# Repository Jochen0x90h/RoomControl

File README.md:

RoomControl
===========
Smart home room controller based on nRF52840 with MQTT and and IEEE 802.15.4 radio support. 
Buttons and relays for lights and blinds can also be connected with a local bus using 
LIN physical layer.

Control
-------
This is a 3D printed box with a display and digital potentiometer that gets installed in each
room instead of the floor heating thermostat. It can control the heating valve using an opto-triac,
connect to light and blind switches and relays using LIN physical layer and to battery-free switches
(EnOcan) using an IEEE 802.15.4 radio interface.

Switch
------
This is a wall switch and actor for lights and blinds that can be mounted behind Eltako E-Design
frames and rockers. It connects to the Control via a bus based on LIN physical layer.

Gateway
-------
This is a hat for rpi or compatible single board computers that connects to multiple Controls
via a IEEE 802.15.4 radio network and to an MQTT broker such as mosquitto.

License
-------
This work is licensed under a
[Creative Commons Attribution-NonCommercial-ShareAlike 4.0 International License][cc-by-nc-sa].

[![CC BY-NC-SA 4.0][cc-by-nc-sa-image]][cc-by-nc-sa]

[cc-by-nc-sa]: http://creativecommons.org/licenses/by-nc-sa/4.0/
[cc-by-nc-sa-image]: https://licensebuttons.net/l/by-nc-sa/4.0/88x31.png

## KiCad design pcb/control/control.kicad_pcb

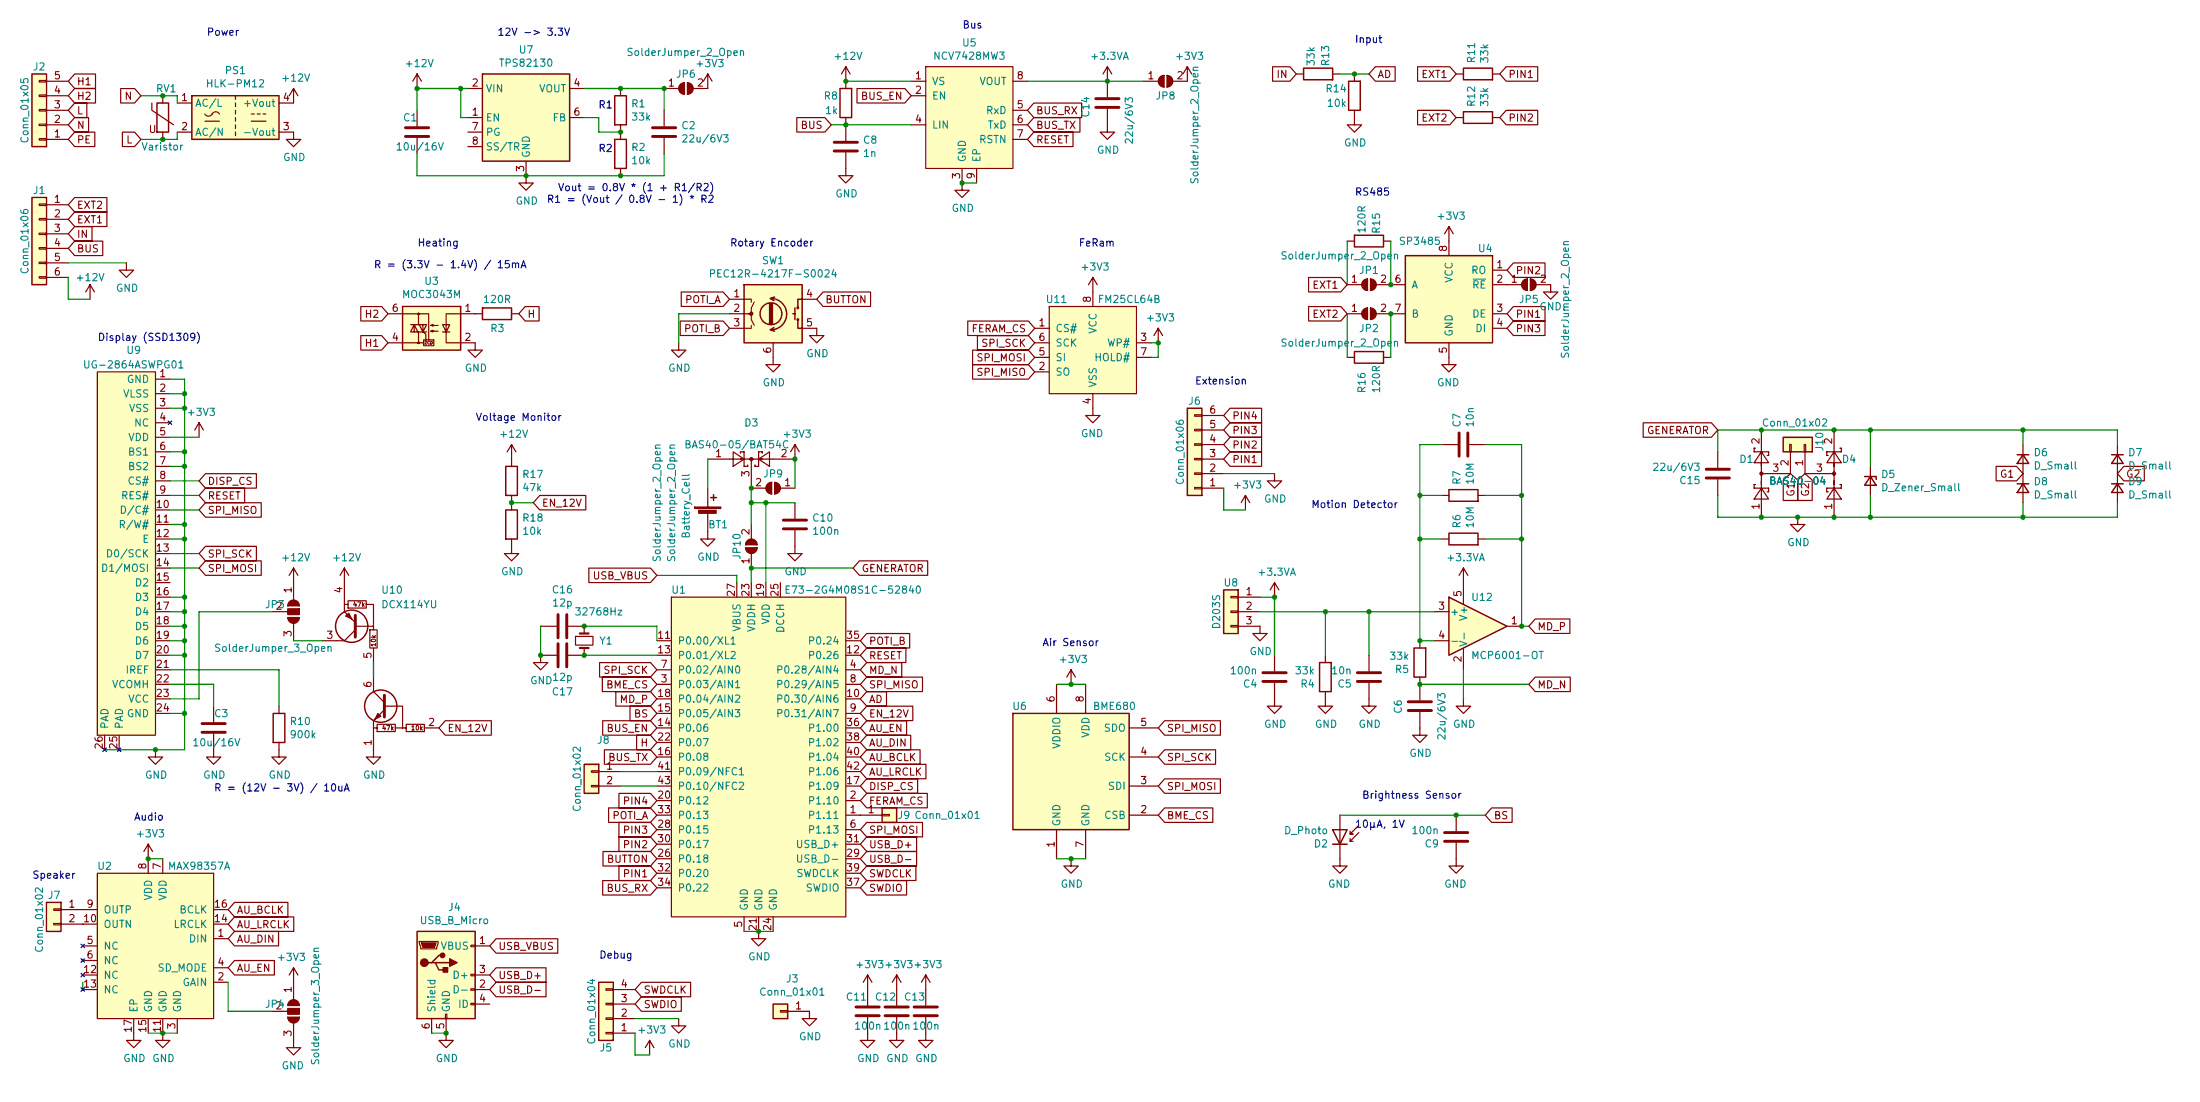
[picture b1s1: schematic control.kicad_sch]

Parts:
BT1: Battery_Cell; Battery_2032
C1, C3: 10u/16V; C_1206_3216Metric
C2, C6, C14, C15: 22u/6V3; C_0805_2012Metric
C4, C9, C10, C11, C12, C13: 100n; C_0603_1608Metric
C5, C7: 10n; C_0603_1608Metric
C8: 1n; C_0603_1608Metric
C16, C17: 12p; C_0603_1608Metric
D1, D4: BAS40-04; SOT-23
D2: D_Photo; DiodeHoles
D3: BAS40-05/BAT54C; SOT-23
D5: D_Zener_Small; D_SOD-323F
D6, D7, D8, D9: D_Small; D_1206_3216Metric_Castellated
J1: Conn_01x06; Wago_236-406
J2: Conn_01x05; Wago_236-405
J3: Conn_01x01; PinHeader_1x01_P2.54mm_Vertical
J4: USB_B_Micro; USB_Micro-B
J5: Conn_01x04; PinHeader_1x04_P2.00mm_Vertical
J6: Conn_01x06; PinHeader_1x06_P2.54mm_Vertical
J7, J10: Conn_01x02; PinHeader_1x02_P2.54mm_Vertical
J8: Conn_01x02; PinHeader_1x02_P2.00mm_Vertical
J9: Conn_01x01; TestPoint_Pad_1.5x1.5mm
JP1, JP2, JP5, JP6, JP8, JP9, JP10: SolderJumper_2_Open; Jumper2
JP3, JP4: SolderJumper_3_Open; Jumper3
PS1: HLK-PM12; HLK-PMxx
R1, R4, R5: 33k; R_0603_1608Metric
R2, R14, R18: 10k; R_0603_1608Metric
R3, R15, R16: 120R; R_1206_3216Metric
R6, R7: 10M; R_0603_1608Metric
R8: 1k; R_1206_3216Metric
R10: 900k; R_0603_1608Metric
R11, R12, R13: 33k; R_1206_3216Metric
R17: 47k; R_0603_1608Metric
RV1: Varistor; S10K275
SW1: PEC12R-4217F-S0024; PEC12R
U1: E73-2G4M08S1C-52840
U2: MAX98357A
U3: MOC3043M
U4: SP3485; SOIC-8_3.9x4.9mm_P1.27mm
U5: NCV7428MW3; NCV7428MW
U6: BME680
U7: TPS82130
U8: D203S
U9: UG-2864ASWPG01; Connector-Flat-24_P0.5mm
U10: DCX114YU; SOT-363_SC-70-6
U11: FM25CL64B
U12: MCP6001-OT; SOT-23-5
Y1: 32768Hz; Crystal_DS26_D2.0mm_L6.0mm_Vertical

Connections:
+3.3VA: C4.2, C14.2, JP8.1 (A), U5.8 (VOUT), U8.1, U12.5 (V+)
+3V3: C11.2, C12.2, C13.2, D3.2, J5.1, J6.1, JP4.1 (A), JP6.2 (B), JP8.2 (B), JP9.1 (A), U2.7 (VDD), U2.8 (VDD), U4.8 (VCC), U6.6 (VDDIO), U6.8 (VDD), U9.5 (VDD), U11.3 (WP#), U11.7 (HOLD#), U11.8 (VCC)
+12V: C1.1, J1.6, JP3.1 (A), PS1.4 (+Vout), R8.2, R17.1, U5.1 (VS), U7.1 (EN), U7.2 (VIN), U10.4 (C2)
AD: R13.2, R14.2, U1.10 (P0.30/AIN6)
AU_BCLK: U1.40 (P1.04), U2.16 (BCLK)
AU_DIN: U1.38 (P1.02), U2.1 (DIN)
AU_EN: U1.36 (P1.00), U2.4 (SD_MODE)
AU_LRCLK: U1.42 (P1.06), U2.14 (LRCLK)
BME_CS: U1.3 (P0.03/AIN1), U6.2 (CSB)
BS: C9.2, D2.2 (A), U1.15 (P0.05/AIN3)
BUS: C8.1, J1.4, R8.1, U5.4 (LIN)
BUS_EN: U1.14 (P0.06), U5.2 (EN)
BUS_RX: U1.34 (P0.22), U5.5 (RxD)
BUS_TX: U1.16 (P0.08), U5.6 (TxD)
BUTTON: SW1.4 (S1), U1.26 (P0.18)
DISP_CS: U1.17 (P1.09), U9.8 (CS#)
EN_12V: R17.2, R18.1, U1.9 (P0.31/AIN7), U10.2 (B1)
EXT1: J1.2, JP1.1 (A), R11.1, R15.2
EXT2: J1.1, JP2.1 (A), R12.1, R16.1
FERAM_CS: U1.2 (P1.10), U11.1 (CS#)
G1: D1.3, D6.2 (A), D8.1 (K), J10.2
G2: D4.3, D7.2 (A), D9.1 (K), J10.1
GENERATOR: C15.2, D1.2, D4.2, D5.1 (K), D6.1 (K), D7.1 (K), JP10.1 (A), U1.23 (VDDH)
GND: BT1.2 (-), C1.2, C2.2, C3.2, C4.1, C5.1, C6.1, C8.2, C9.1, C10.2, C11.1, C12.1, C13.1, C14.1, C15.1, C16.2, C17.2, D1.1, D2.1 (K), D4.1, D5.2 (A), D8.2 (A), D9.2 (A), J1.5, J3.1, J4.5 (GND), J4.6 (Shield), J5.2, J6.2, JP4.3 (B), JP5.2 (B), PS1.3 (-Vout), R2.2, R4.1, R10.2, R14.1, R18.2, SW1.2 (C), SW1.5 (S2), SW1.6 (SH), U1.5 (GND), U1.21 (GND), U1.24 (GND), U2.3 (GND), U2.11 (GND), U2.15 (GND), U2.17 (EP), U3.2, U4.5 (GND), U5.3 (GND), U5.9 (EP), U6.1 (GND), U6.7 (GND), U7.3 (GND), U7.9 (GND), U8.3, U9.1 (GND), U9.2 (VLSS), U9.3 (VSS), U9.6 (BS1), U9.7 (BS2), U9.11 (R/W#), U9.12 (E), U9.16 (D3), U9.17 (D4), U9.18 (D5), U9.19 (D6), U9.20 (D7), U9.24 (GND), U9.25 (PAD), U9.26 (PAD), U10.1 (E1), U11.4 (VSS), U12.2 (V-)
H: R3.1, U1.22 (P0.07)
H1: J2.5, U3.4
H2: J2.4, U3.6
IN: J1.3, R13.1
L: J2.3, PS1.2 (AC/N), RV1.2
MD_N: C6.2, R5.1, U1.4 (P0.28/AIN4)
MD_P: C7.2, R6.2, R7.2, U1.18 (P0.04/AIN2), U12.1
N: J2.2, PS1.1 (AC/L), RV1.1
unnamed: BT1.1 (+), D3.1
unnamed: C2.1, JP6.1 (A), R1.1, U7.4 (VOUT), U7.5 (VOUT)
unnamed: C3.1, U9.22 (VCOMH)
unnamed: C5.2, R4.2, U8.2, U12.3 (+)
unnamed: C7.1, R5.2, R6.1, R7.1, U12.4 (-)
unnamed: C10.1, D3.3, JP9.2 (B), JP10.2 (B), U1.19 (VDD)
unnamed: C16.1, U1.11 (P0.00/XL1), Y1.1
unnamed: C17.1, U1.13 (P0.01/XL2), Y1.2
unnamed: J7.1, U2.9 (OUTP)
unnamed: J7.2, U2.10 (OUTN)
unnamed: J8.1, U1.41 (P0.09/NFC1)
unnamed: J8.2, U1.43 (P0.10/NFC2)
unnamed: J9.1, U1.1 (P1.11)
unnamed: JP1.2 (B), R15.1, U4.6 (A)
unnamed: JP2.2 (B), R16.2, U4.7 (B)
unnamed: JP3.2 (C), U9.23 (VCC)
unnamed: JP3.3 (B), U10.3 (C2)
unnamed: JP4.2 (C), U2.2 (GAIN)
unnamed: JP5.1 (A), U4.2 (~RE)
unnamed: R1.2, R2.1, U7.6 (FB)
unnamed: R3.2, U3.1
unnamed: R10.1, U9.21 (IREF)
unnamed: U10.5 (B2), U10.6 (C1)
PE: J2.1
PIN1: J6.3, R11.2, U1.32 (P0.20), U4.3 (DE)
PIN2: J6.4, R12.2, U1.30 (P0.17), U4.1 (RO)
PIN3: J6.5, U1.28 (P0.15), U4.4 (DI)
PIN4: J6.6, U1.20 (P0.12)
POTI_A: SW1.1 (A), U1.33 (P0.13)
POTI_B: SW1.3 (B), U1.35 (P0.24)
RESET: U1.12 (P0.26), U5.7 (RSTN), U9.9 (RES#)
SPI_MISO: U1.8 (P0.29/AIN5), U6.5 (SDO), U9.10 (D/C#), U11.2 (SO)
SPI_MOSI: U1.6 (P1.13), U6.3 (SDI), U9.14 (D1/MOSI), U11.5 (SI)
SPI_SCK: U1.7 (P0.02/AIN0), U6.4 (SCK), U9.13 (D0/SCK), U11.6 (SCK)
SWDCLK: J5.4, U1.39 (SWDCLK)
SWDIO: J5.3, U1.37 (SWDIO)
USB_D+: J4.3 (D+), U1.31 (USB_D+)
USB_D-: J4.2 (D-), U1.29 (USB_D-)
USB_VBUS: J4.1 (VBUS), U1.27 (VBUS)

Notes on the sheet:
FeRam
R = (3.3V - 1.4V) / 15mA
Vout = 0.8V * (1 + R1/R2) R1 = (Vout / 0.8V - 1) * R2
10µA, 1V
Input
Bus
Debug
Brightness Sensor
RS485
Extension
Rotary Encoder
R = (12V - 3V) / 10uA
Power
Speaker
12V -> 3.3V
Voltage Monitor
Motion Detector
Audio
Air Sensor
Heating
Display (SSD1309)

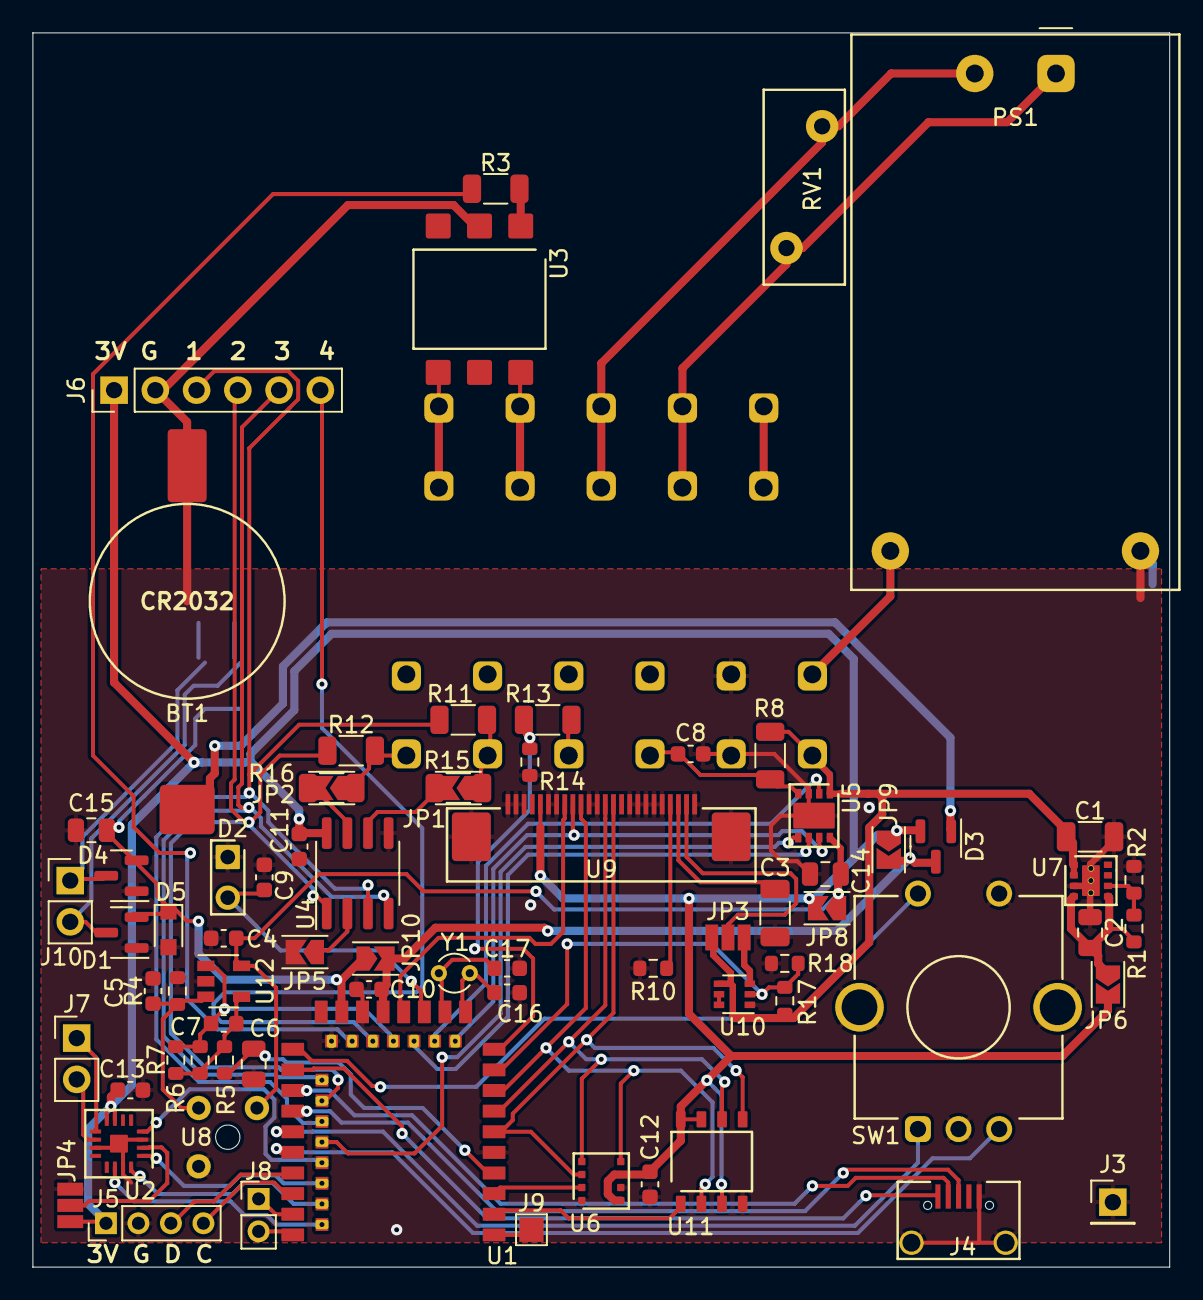
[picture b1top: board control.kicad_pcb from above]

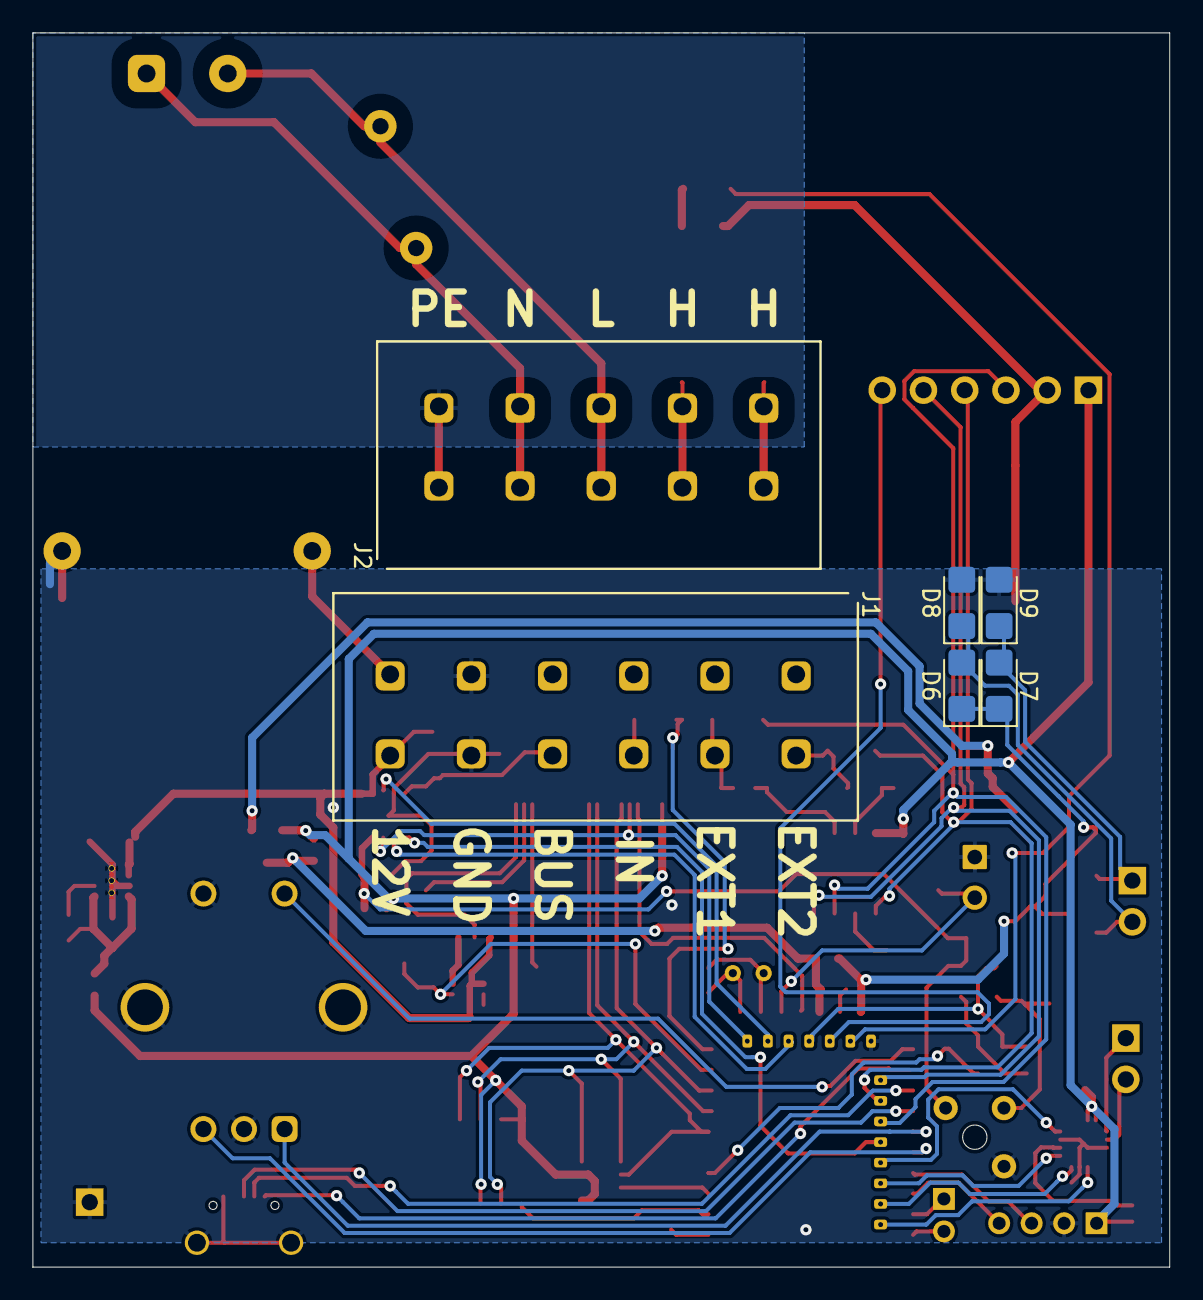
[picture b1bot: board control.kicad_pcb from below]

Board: 2 copper layers, 70.0 x 76.0 mm, 79 parts (6 on the bottom side), 70 nets.

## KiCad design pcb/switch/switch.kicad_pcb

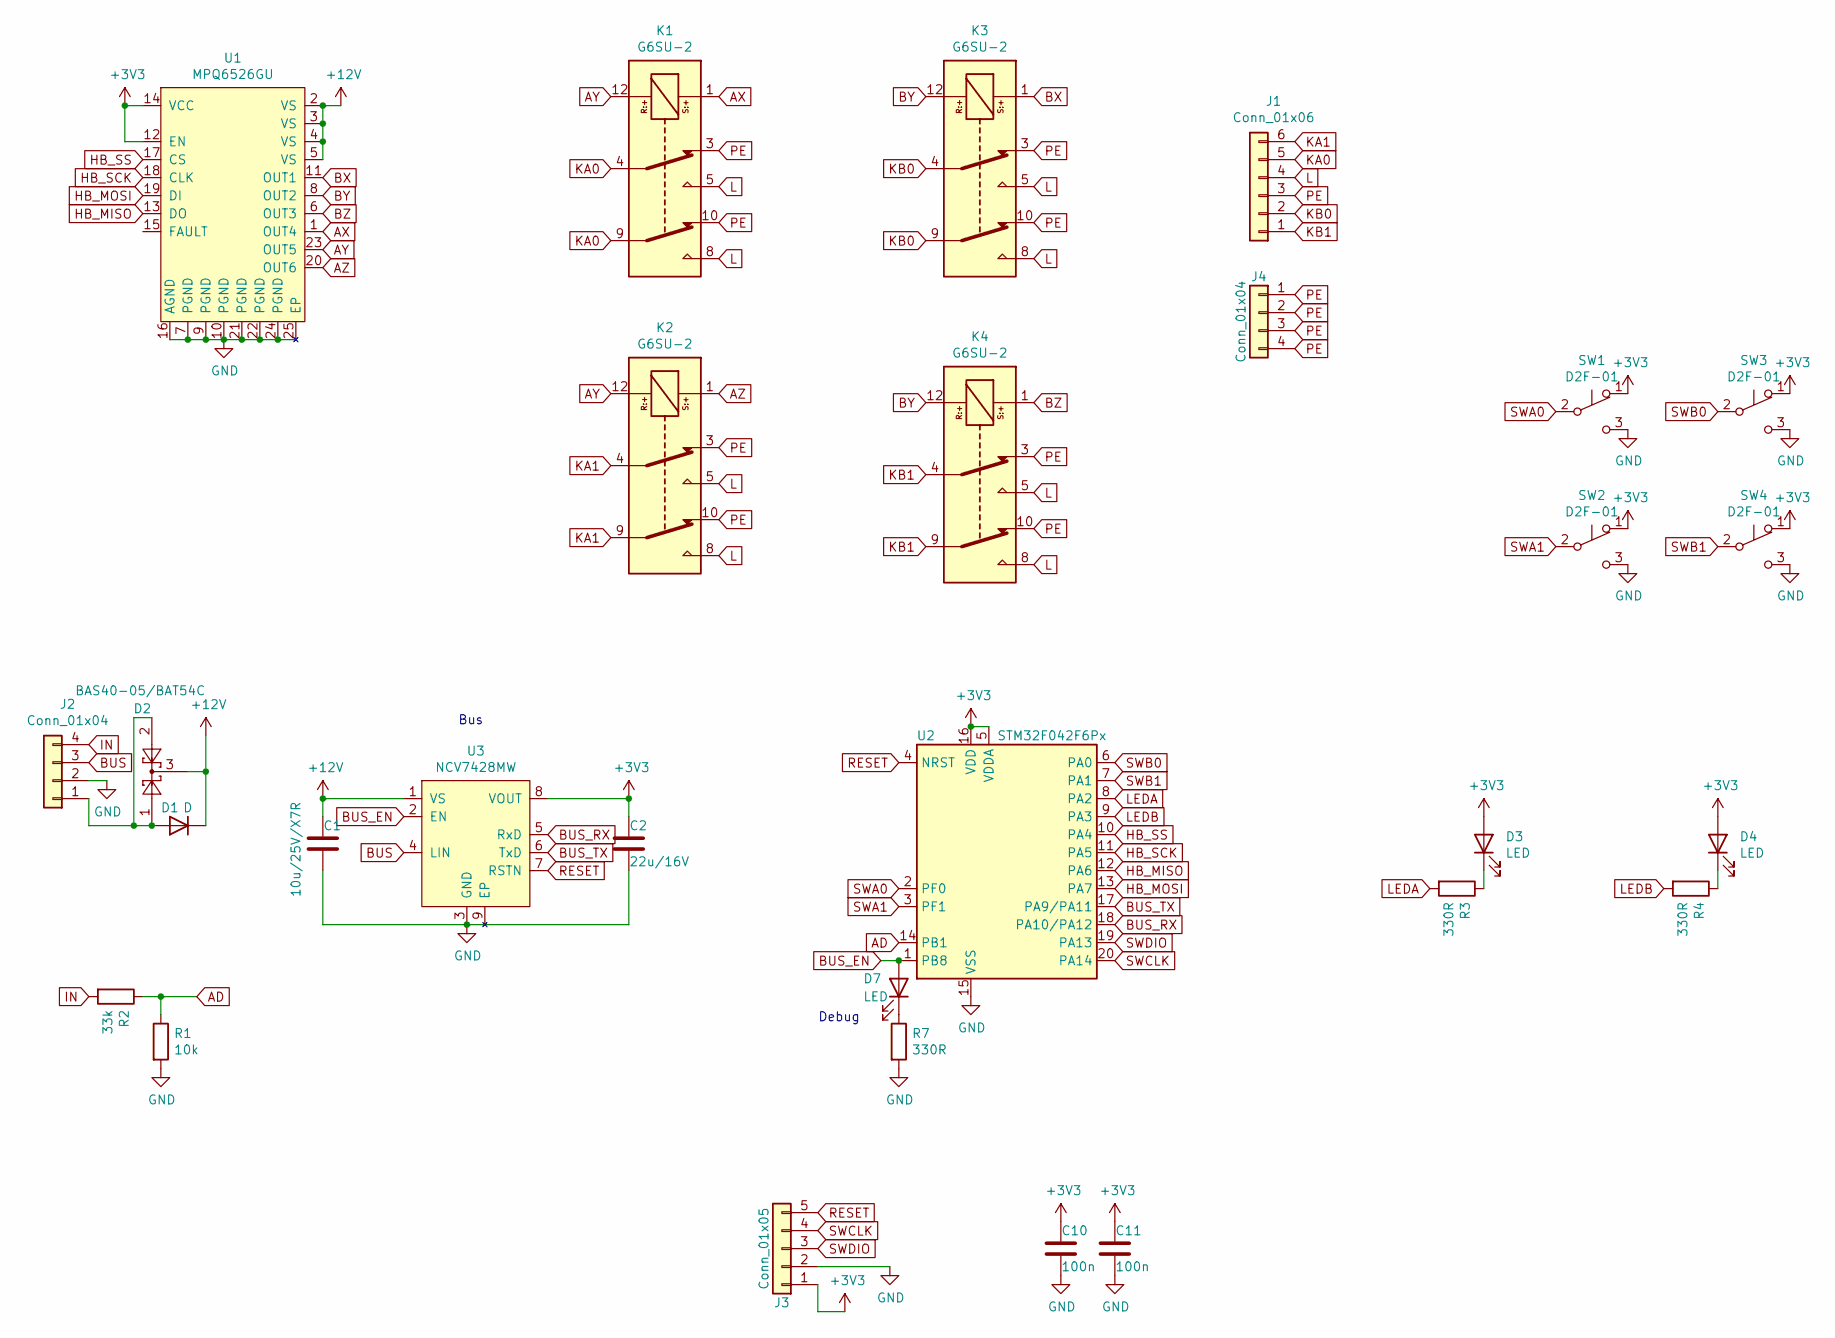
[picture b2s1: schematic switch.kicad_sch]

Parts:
C1: 10u/25V/X7R; C_1206_3216Metric
C2: 22u/16V; C_0805_2012Metric
C10, C11: 100n; C_0603_1608Metric
D1: D; D_1206_3216Metric_Castellated
D2: BAS40-05/BAT54C; SOT-23
D3, D4: LED; DiodeHolesSwitch
D7: LED; LED_0805_2012Metric_Castellated
J1: Conn_01x06; Wago_236-406
J2: Conn_01x04; Wago_236-404
J3: Conn_01x05; PinHeader_1x05_P2.00mm_Vertical
J4: Conn_01x04; Switch_Mount
K1, K2, K3, K4: G6SU-2
R1: 10k; R_0603_1608Metric
R2: 33k; R_1206_3216Metric
R3, R4, R7: 330R; R_0603_1608Metric
SW1, SW2, SW3, SW4: D2F-01
U1: MPQ6526GU
U2: STM32F042F6Px; STM32F042F6
U3: NCV7428MW

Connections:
+3V3: C2.1, C10.1, C11.1, D3.2 (A), D4.2 (A), J3.1, SW1.1 (A), SW2.1 (A), SW3.1 (A), SW4.1 (A), U1.12 (EN), U1.14 (VCC), U2.5 (VDDA), U2.16 (VDD), U3.8 (VOUT)
+12V: C1.1, D1.1 (K), D2.3, U1.2 (VS), U1.3 (VS), U1.4 (VS), U1.5 (VS), U3.1 (VS)
AD: R1.1, R2.1, U2.14 (PB1)
AX: K1.1, U1.1 (OUT4)
AY: K1.12, K2.12, U1.23 (OUT5)
AZ: K2.1, U1.20 (OUT6)
BUS: J2.3, U3.4 (LIN)
BUS_EN: D7.2 (A), U2.1 (PB8), U3.2 (EN)
BUS_RX: U2.18 (PA10/PA12), U3.5 (RxD)
BUS_TX: U2.17 (PA9/PA11), U3.6 (TxD)
BX: K3.1, U1.11 (OUT1)
BY: K3.12, K4.12, U1.8 (OUT2)
BZ: K4.1, U1.6 (OUT3)
GND: C1.2, C2.2, C10.2, C11.2, J2.2, J3.2, R1.2, R7.2, SW1.3 (C), SW2.3 (C), SW3.3 (C), SW4.3 (C), U1.7 (PGND), U1.9 (PGND), U1.10 (PGND), U1.16 (AGND), U1.21 (PGND), U1.22 (PGND), U1.24 (PGND), U1.25 (EP), U2.15 (VSS), U3.3 (GND), U3.9 (EP)
HB_MISO: U1.13 (DO), U2.12 (PA6)
HB_MOSI: U1.19 (DI), U2.13 (PA7)
HB_SCK: U1.18 (CLK), U2.11 (PA5)
HB_SS: U1.17 (CS), U2.10 (PA4)
IN: J2.4, R2.2
KA0: J1.5, K1.4, K1.9
KA1: J1.6, K2.4, K2.9
KB0: J1.2, K3.4, K3.9
KB1: J1.1, K4.4, K4.9
L: J1.4, K1.5, K1.8, K2.5, K2.8, K3.5, K3.8, K4.5, K4.8
LEDA: R3.2, U2.8 (PA2)
LEDB: R4.2, U2.9 (PA3)
unnamed: D1.2 (A), D2.1, D2.2, J2.1
unnamed: D3.1 (K), R3.1
unnamed: D4.1 (K), R4.1
unnamed: D7.1 (K), R7.1
PE: J1.3, J4.1, J4.2, J4.3, J4.4, K1.3, K1.10, K2.3, K2.10, K3.3, K3.10, K4.3, K4.10
RESET: J3.5, U2.4 (NRST), U3.7 (RSTN)
SWA0: SW1.2 (B), U2.2 (PF0)
SWA1: SW2.2 (B), U2.3 (PF1)
SWB0: SW3.2 (B), U2.6 (PA0)
SWB1: SW4.2 (B), U2.7 (PA1)
SWCLK: J3.4, U2.20 (PA14)
SWDIO: J3.3, U2.19 (PA13)

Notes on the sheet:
Debug
Bus

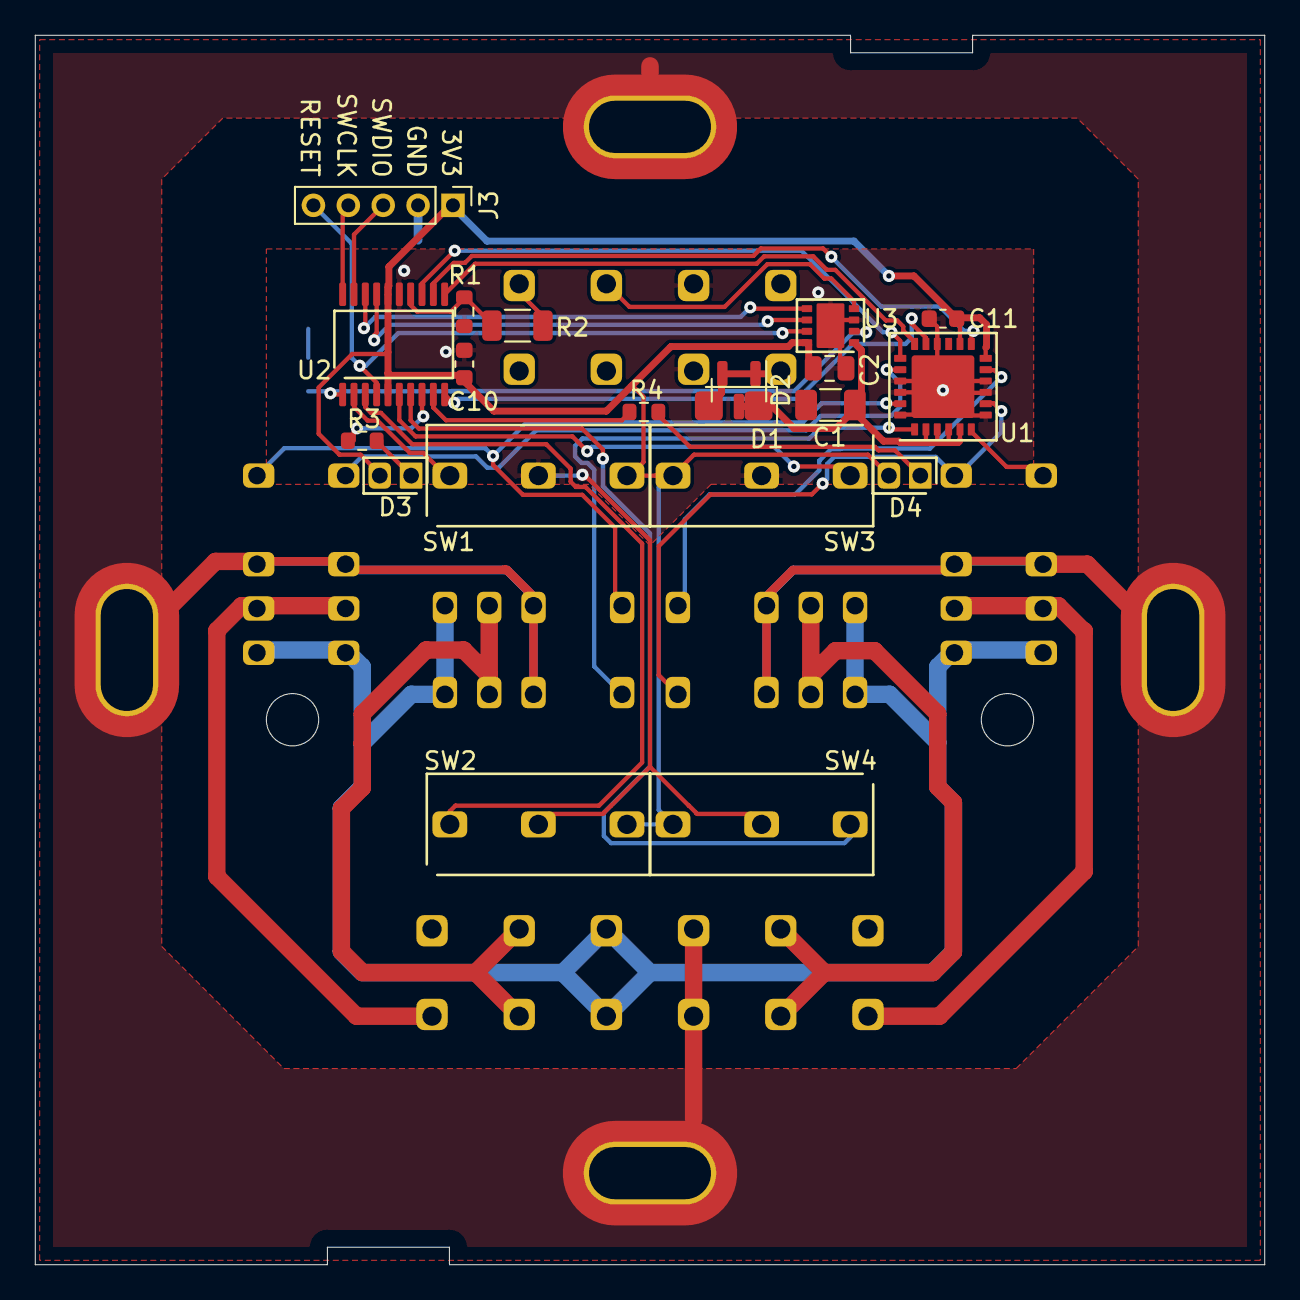
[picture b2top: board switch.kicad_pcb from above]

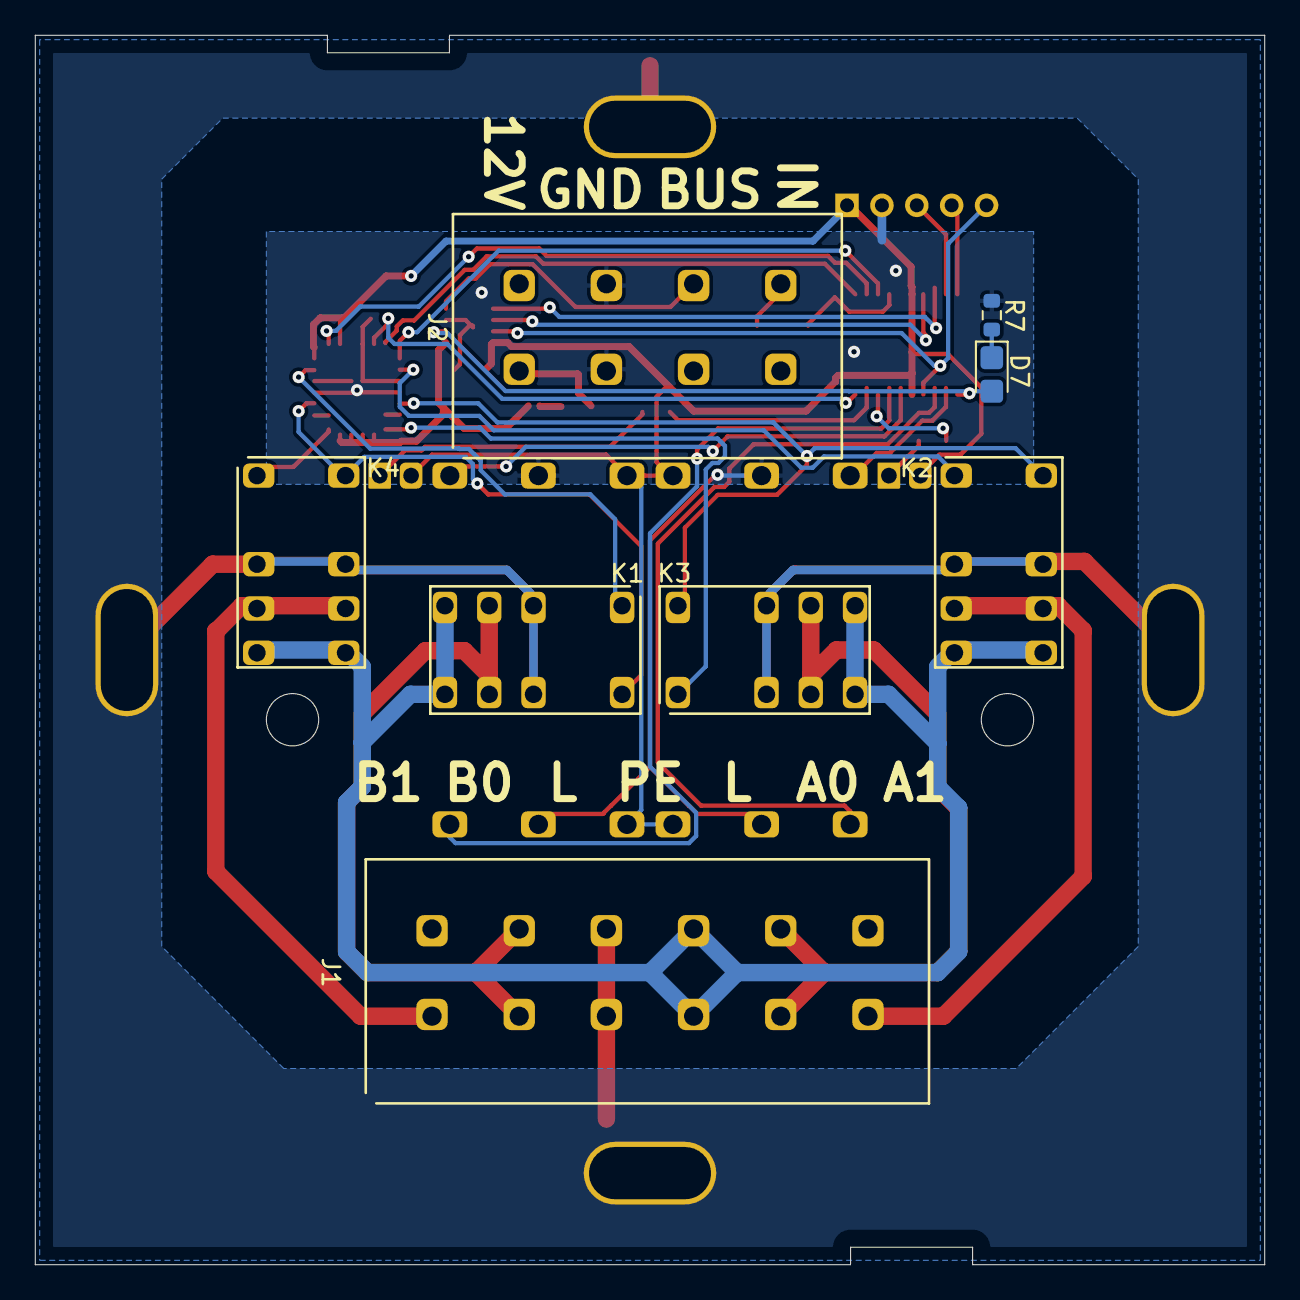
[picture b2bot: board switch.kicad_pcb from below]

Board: 2 copper layers, 70.5 x 70.5 mm, 29 parts (8 on the bottom side), 38 nets.

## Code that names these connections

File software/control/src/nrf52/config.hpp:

#pragma once

// flash
// -----

// https://infocenter.nordicsemi.com/index.jsp?topic=%2Fps_nrf52840%2Fnvmc.html&cp=4_0_0_3_2
constexpr int FLASH_PAGE_SIZE = 4096;
constexpr int FLASH_PAGE_COUNT = 16;
constexpr int FLASH_WRITE_ALIGN = 4;


// timer
// -----
constexpr int TIMER_COUNT = 4;


// pins
// ----
constexpr int PORT0 = 0;
constexpr int PORT1 = 32;
constexpr int Disconnected = 0xffffffff;

// reset
constexpr int RESET_PIN = PORT0 | 26;

// digital potentiometer
#define HAVE_POTI
constexpr int POTI_A_PIN = PORT0 | 13;
constexpr int POTI_B_PIN = PORT0 | 24;
constexpr int BUTTON_PIN = PORT0 | 18;

// spi: display, air sensor, fe-ram
#define HAVE_SPI
constexpr int SPI_SCK_PIN = PORT0 | 2;
constexpr int SPI_MOSI_PIN = PORT1 | 13;
constexpr int SPI_MISO_PIN = PORT0 | 29; // also connected to display D/C#
constexpr int DISPLAY_CS_PIN = PORT0 | 31;
constexpr int AIR_SENSOR_CS_PIN = PORT0 | 3;
constexpr int FE_RAM_CS_PIN = PORT0 | 8;

// audio
#define HAVE_AUDIO
constexpr int AUDIO_EN_PIN = PORT1 | 0;
constexpr int AUDIO_BCLK_PIN = PORT1 | 4;
constexpr int AUDIO_LRCLK_PIN = PORT1 | 6;
constexpr int AUDIO_DIN_PIN = PORT1 | 2;

// motion detector
constexpr int MOTION_DETECTOR_COMP_PIN = PORT0 | 4;
constexpr int MOTION_DETECTOR_DS_PIN = PORT0 | 12; // delta-sigma

// brightness sensor
constexpr int BRIGHTNESS_SENSOR_PIN = PORT0 | 5;

// heating
constexpr int HEATING_PIN = PORT0 | 7;

// ad input
constexpr int AD_PIN = PORT0 | 30;

// bus
#define HAVE_BUS
constexpr int BUS_EN_PIN = PORT0 | 6;
constexpr int BUS_TX_PIN = PORT0 | 8;
constexpr int BUS_RX_PIN = PORT0 | 22;

// ext pins
constexpr int EXT_PIN1_PIN = PORT0 | 20;
constexpr int EXT_PIN2_PIN = PORT0 | 17;
constexpr int EXT_PIN3_PIN = PORT0 | 15;

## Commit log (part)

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2021-01-15 Add control, switch and software
2021-01-29 New directory structure and nrf52 os layer
2021-03-15 New emulator drivers for timer, calendar, poti and display
2021-03-15 Drivers for air sensor, display, and new Interface class for local and bus devices
2021-03-15 BME680Test works, Add devices menu entries, several fixes
2021-03-15 Add usb driver
2021-03-15 Send queue for BusInterface
2021-03-15 Add greenPowerTest to test commissioning of e.g. PTM215Z
2021-03-15 Put system functions into separate directory
2021-03-21 Add RadioInterface
2021-03-27 Add event loop and timer::allocate()
2021-04-22 Add simple sniffer that writes .pcap files and analyzes packets
2021-05-15 Updated build system
2021-05-19 Filter, send and ack for radio driver
2021-05-30 Radio device can receive and send, separation of sysConfig and appConfig
2021-06-25 Start using coroutines
2021-08-03 First implementation of association
2021-08-03 First implementation of association (#1)
2021-11-16 New method for publishing/subscribing to interfaces, zbee routing
2021-11-17 New method for publishing/subscribing to interfaces, zbee routing (#2)
2021-12-10 Port mqtt-sn to coroutines
2021-12-27 New mqtt-sn broker
2022-01-05 mqtt-sn broker supports client connections
2022-01-12 Add separate forwarder to mqtt-sn broker
2022-01-29 Refactoring, fized size Array and new stream concept
2022-02-01 New mqtt-sn broker based on coroutines (#3)
    Add new stream concept and terminal
2022-02-12 Better zbee zupport
2022-02-12 Better zbee zupport (#4)
2022-02-16 New input abstraction, renamed/moved sysConfig to boardConfig
2022-02-16 New input abstraction, renamed/moved sysConfig to boardConfig (#5)
2022-02-18 SPI supports data/command, remove separate display interface
2022-02-18 SPI supports data/command, remove separate display interface (#6)
2022-02-20 Change system interfaces to uppercase
2022-02-20 Change system interfaces to uppercase (#7)
2022-03-03 Use conan 2 style cmake integration, also compile for target using cmake
2022-03-13 Mac OS compatibility
2022-03-15 Fix minor bug
2022-03-15 Conan2 (#8)
    Use conan 2 style cmake integration, also compile for target using cmake
2022-03-18 Add support for stm32f0
2022-03-19 Add support for stm32f0 (#9)
2022-03-25 Add emulator for switch
2022-04-09 Finish switch emulator
2022-04-09 Renamed Usb to UsbDevice
2022-04-09 Fix M_PI
2022-04-09 Add switch software (#11)
2022-04-17 Add alarms as interface
2022-04-17 Moved .editorconfig to toplevel
2022-04-17 Add alarms as interface (#12)
2022-05-05 Add simple switch and timeout switch
2022-05-20 intermediate commit
2022-05-26 Input/output conversion working
2022-05-27 Alarms emit only trigger messages
2022-06-01 New publishing scheme
2022-06-04 indents and minor fix
2022-06-04 Functions (#13)
    * Functions for light, blind and heating
    * New publishing scheme
2022-06-04 Add mDNS sniffer
2022-06-05 More dns types
2022-06-05 Macos compatibility
2022-06-06 Posix drivers are basis for emu drivers
2022-06-07 Minor fixes
2022-06-08 Add ANY type
2022-06-09 Minor refactoring
2022-06-09 Mdns (#14)
    Add mDNS sniffer
2022-06-22 New message types
2022-06-22 Remove enum warning suppression
2022-06-22 New message types (#15)
2022-07-09 New flash storage
2022-07-12 Use new flash storage in all interfaces
2022-07-12 New flash storage for configuration
2022-07-15 Minor fix
2022-07-15 New storage (#16)
    New flash key/value storage inspired by Zephyr and ESP32
2022-07-24 Add color light functions and refactor Interface
2022-08-06 Add color light functions and refactor Interface (#17)
2022-08-06 Add sound support
2022-08-08 Add sound types
2022-08-13 Minor stuff
2022-08-13 Sound support (#18)
2022-08-14 Fix radio and usb drivers
2022-08-27 Fix radio driver
2022-08-28 fix CMakeLists
2022-08-28 restore RadioTest
2022-08-28 Fix USB and radio drivers (#19)
2022-09-04 Start BLE support
2022-09-04 Start BLE support (#20)
2022-09-12 New connections
2022-09-17 New connections work for all interfaces
2022-09-20 Optimized WaitlistNode, add separate LinkedList
2022-09-27 Add listeners
2022-09-27 Add AwaitableMove test
2022-09-27 New Connections (#21)
2022-10-06 Add display listeners
2022-10-10 Add control by wheel
2022-10-11 Add missing file
2022-10-11 id -> deviceId
2022-10-12 MacOS fixes
2022-10-13 Message Listeners (#22)
    * Add display listeners
    * Add control by wheel
2022-10-15 New SPI and Storage
2022-10-15 add missing drivers
2022-10-16 Add FeRamCounters
2022-10-16 Fix FeRamCounters
2022-10-17 Fix include error
2022-10-22 New QuadratureDecoder and BusInterface
2022-10-22 New BusNode
2022-10-22 new dependencies
2022-10-22 new glfw
2022-10-22 Debug InputTest and QadraturedecoderTest
2022-10-27 Fix security counters
2022-10-27 New drivers (#23)
    * SPI, Storage, BusMaster, BusNode, QuadratureDecoder
2022-11-03 Add FlashStorage
2022-11-03 cleanup
2022-11-03 Add Flash for stm32f0
2022-11-05 Flash support for switch
2022-11-05 New nrf52 files
2022-11-05 Flash support (#24)
2022-11-12 Add FeRam and extension header to pcb
2022-11-14 Test circuit for generator, switch: LEDs at center
2022-11-18 1st prototype of pcb
2022-11-18 Switch to KiCad 6
2022-11-18 Also update switch to KiCad 6
2022-11-19 Port symbol library to KiCad 6
2022-11-20 First prototype of PCB and switch to KiCad 6 (#25)
2022-12-17 Implement BusNode driver and improve other drivers
2022-12-20 Windows compatibility and new UsbDevice driver
2022-12-24 Windows compatibility
2022-12-24 Linux compatibility
2022-12-25 Integrate Loop and Timer into loop
